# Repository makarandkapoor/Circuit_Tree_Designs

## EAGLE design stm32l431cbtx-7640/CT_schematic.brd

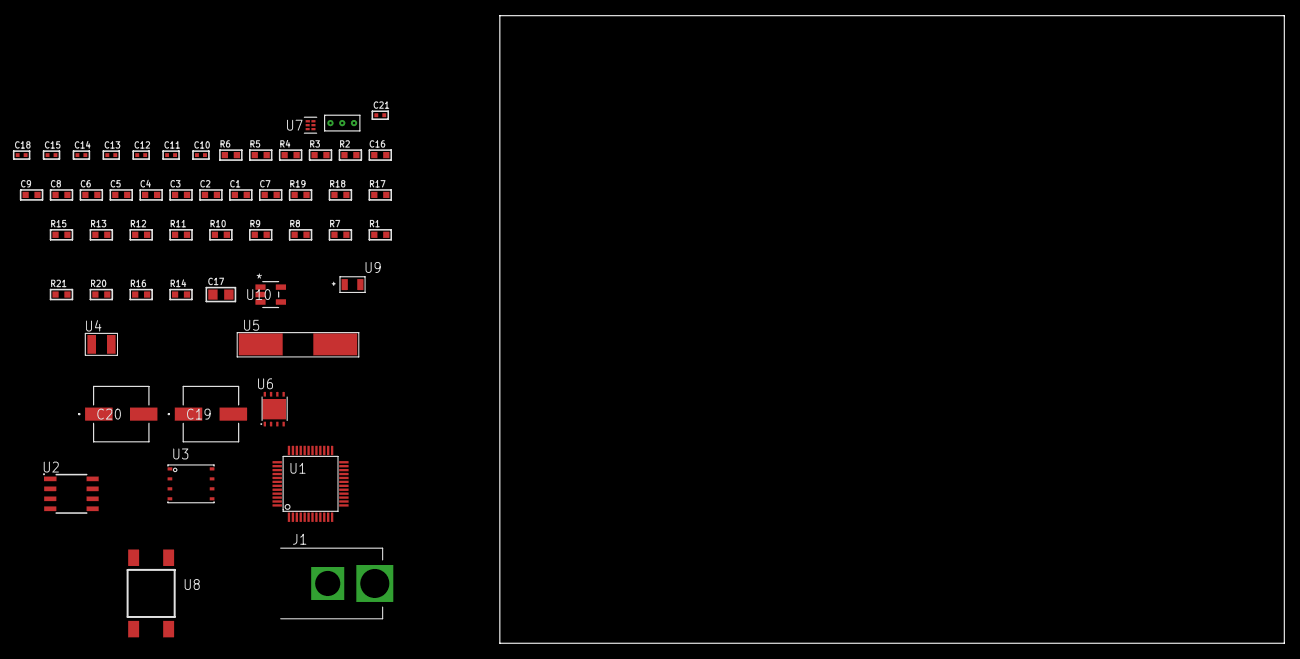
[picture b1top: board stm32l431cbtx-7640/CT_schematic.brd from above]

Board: 2 copper layers, 100.0 x 80.0 mm, 54 parts (0 on the bottom side), 30 nets, no tracks yet.

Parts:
C1, C9: 1e-06; C0603
C2, C3, C4, C5, C6: 1e-07; C0603
C7: 4.7e-06; C0603
C8: 1e-08; C0603
C10, C11, C12, C13: 1e-11; C0402
C14, C15, C21: 1e-08; C0402
C16: 8e-07; R0603
C17: 1e-05; C0805
C18: 1e-07; C0402
C19, C20: 0.0001; EXV-9H
J1: PJ-037B; PJ-037B_PACKAGE
R1, R7, R8, R9, R10, R11, R12, R13, R17, R18: 10000.0; R0603
R2: 1000.0; R0603
R3: 910.0; R0603
R4: 4700.0; R0603
R5, R6: 2200.0; R0603
R14, R16: 100000.0; R0603
R15: 36000.0; R0603
R19: 82000.0; R0603
R20: 300000.0; R0603
R21: 120000.0; R0603
U1: STM32L431CBT6; LQFP48
U2: AT25256B-SSHL-T; SOIC-8
U3: 24AA256-I/MF; DFN8-S
U4: ABS07-32.768KHZ-7-T
U5: ABLS-25.000MHZ-B2F-T
U6: LP2951ACSDX/NOPB; WSON-8
U7: TPS3895ADRYR; SON-6
U8: 4-1437565-2; SW_4-1437565-2
U9: Q65110A2395; LGM67K-G1J2-24-Z
U10: nc7sz125m5x; NC7SZ125M5X
U11: Dummy; DUMMY_PACKAGE_111

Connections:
CLK_CRYSTAL_U1_3: C10.1, U1.3, U4.1
CLK_CRYSTAL_U1_4: C11.1, U1.4, U4.2
CLK_CRYSTAL_U1_5: C12.1, U1.5, U5.1
CLK_CRYSTAL_U1_6: C13.1, U1.6, U5.2
GND: C1.2, C2.2, C3.2, C4.2, C5.2, C6.2, C7.2, C8.2, C9.2, C10.2, C11.2, C12.2, C13.2, C14.2, C15.2, C16.2, C17.2, C18.2, C19.2, C20.2, C21.2, J1.2, R2.2, R7.2, R11.2, R12.2, R16.2, R19.2, R21.2, U1.8, U1.23, U1.35, U1.47, U2.4, U3.4, U6.3, U6.4, U6.PAD, U7.2, U9.C, U10.1, U10.3, U11.1
NET_U1_7: R4.1, U1.7, U10.4
NET_U1_30: R5.1, U1.30, U3.6
NET_U1_31: R6.1, U1.31, U3.5
NET_U1_44: R7.1, U1.44
NET_U1_45: R3.1, U1.45, U9.A
NET_U1_46: R1.1, U1.46, U8.3, U8.4
NET_U2_3: R8.1, U2.3
NET_U2_7: R10.1, U2.7
NET_U3_1: R11.1, U3.1
NET_U3_2: R12.1, U3.2
NET_U3_3: R13.1, U3.3
NET_U6_5: R14.1, U6.5
NET_U6_7: R15.2, R16.1, U6.7
NET_U7_1: R18.1, R19.1, U7.1
NET_U7_3: R20.2, R21.1, U7.3
NET_U7_4: R17.1, U7.4, U10.2
NET_U8_1: R2.1, U8.1, U8.2
PROC_ADC1_IN10: U1.15, U11.2
PROC_ADC1_IN16: U1.19, U11.3
PROC_SPI1_MISO: U1.16, U2.2
PROC_SPI1_MOSI: U1.17, U2.5
PROC_SPI1_NSS: R9.1, U1.14, U2.1
PROC_SPI1_SCK: U1.11, U2.6
VCC_S1_12V7: C16.1, C19.1, C20.1, J1.1, U6.8
VCC_TIER1_1V8: C1.1, C2.1, C3.1, C4.1, C5.1, C6.1, C7.1, C8.1, C9.1, C14.1, C15.1, C17.1, C18.1, C21.1, R1.2, R3.2, R4.2, R5.2, R6.2, R8.2, R9.2, R10.2, R13.2, R14.2, R15.1, R17.2, R18.2, R20.1, U1.1, U1.9, U1.24, U1.36, U1.48, U2.8, U3.7, U3.8, U6.1, U7.6, U10.5

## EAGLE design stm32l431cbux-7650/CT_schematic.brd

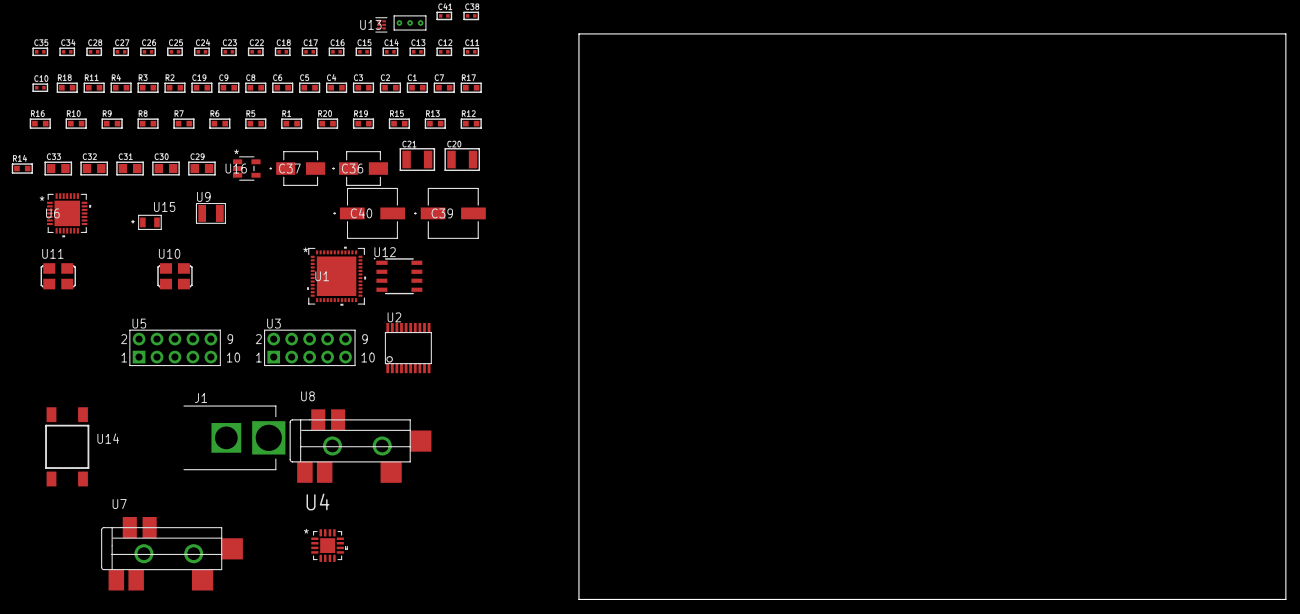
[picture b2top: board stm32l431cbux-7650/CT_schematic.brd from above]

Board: 2 copper layers, 100.0 x 80.0 mm, 79 parts (0 on the bottom side), 50 nets, no tracks yet.

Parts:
C1, C9, C19: 1e-06; C0603
C2, C3, C4, C5, C6: 1e-07; C0603
C7: 4.7e-06; C0603
C8: 1e-08; C0603
C10, C11: 1e-11; C0402
C12, C13, C14, C15, C16, C17, C18, C24, C25, C26, C27, C28, C38: 1e-07; C0402
C20, C21: 2.2e-05; C1210
C22, C23: 1e-09; C0402
C29, C30, C31, C32, C33: 1e-05; C0805
C34, C35, C41: 1e-08; C0402
C36: 1e-06; EXV-9B
C37: 2.2e-06; EXV-9B
C39, C40: 0.0001; EXV-9H
J1: PJ-037B; PJ-037B_PACKAGE
R1, R5, R6, R7, R16, R17: 10000.0; R0603
R2: 1000.0; R0603
R3: 1600.5; R0603
R4: 4700.0; R0603
R8, R9, R10: 47000.0; R0603
R11: 680.0; R0603
R12, R13, R15: 100000.0; R0603
R14: 164658.62; R0603
R18: 9100.0; R0603
R19: 680000.0; R0603
R20: 120000.0; R0603
U1: STM32L431CBU6; UFQFPN48
U2: SP3203ECY-L/TR; TSSOP20-I
U3, U5: HTSS-105-01-G-D
U4: TSC2008TRGVRQ1; QFN65P400X400X100-17N
U6: WM8731CLSEFL; QFN-28
U7, U8: SJ-43515TS-SMT-TR
U9: ABS07-32.768KHZ-7-T
U10: ASFL1-12.288MHZ-EC-T; ASFL1
U11: ASFL1-25MHZ-NCS; ASFL1
U12: LP2954AIMX/NOPB; LP2954
U13: TPS3895ADRYR; SON-6
U14: 4-1437565-2; SW_4-1437565-2
U15: Q65110A2395; LGM67K-G1J2-24-Z
U16: nc7sz125m5x; NC7SZ125M5X
U17: Dummy; DUMMY_PACKAGE_160

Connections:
CLK_CRYSTAL_U1_3: C10.1, U1.3, U9.1
CLK_CRYSTAL_U1_4: C11.1, U1.4, U9.2
CLK_U1_5: U1.5, U11.3
CLK_U6_1: U6.1, U10.3
GND: C1.2, C2.2, C3.2, C4.2, C5.2, C6.2, C7.2, C8.2, C9.2, C10.2, C11.2, C12.2, C13.2, C16.2, C17.2, C18.2, C19.2, C23.2, C24.2, C25.2, C26.2, C27.2, C28.2, C29.2, C30.2, C31.2, C32.2, C33.2, C34.2, C35.2, C36.2, C37.2, C38.2, C39.2, C40.2, C41.2, J1.2, R2.2, R5.2, R8.2, R9.2, R10.2, R15.2, R18.2, R20.2, U1.8, U1.23, U1.35, U1.47, U1.49, U2.18, U3.9, U4.10, U4.12, U4.17, U5.9, U6.4, U6.15, U6.19, U6.25, U6.26, U6.29, U7.1, U8.1, U10.2, U11.2, U12.4, U13.2, U15.C, U16.1, U16.3, U17.1
NET_U1_7: R4.1, U1.7, U16.4
NET_U1_44: R5.1, U1.44
NET_U1_45: R3.1, U1.45, U15.A
NET_U1_46: R1.1, U1.46, U14.3, U14.4
NET_U2_1: C14.1, U2.1
NET_U2_2: C16.1, U2.2
NET_U2_3: C14.2, U2.3
NET_U2_4: C15.1, U2.4
NET_U2_5: C15.2, U2.5
NET_U2_6: C17.1, U2.6
NET_U3_3: U2.14, U3.3
NET_U3_4: U2.13, U3.4
NET_U3_5: U2.17, U3.5
NET_U3_6: U2.16, U3.6
NET_U4_15: R7.1, U4.15
NET_U5_3: U4.7, U5.3
NET_U5_4: U4.9, U5.4
NET_U5_5: U4.6, U5.5
NET_U5_6: U4.8, U5.6
NET_U6_20: C28.1, C33.1, U6.20
NET_U7_2: C21.1, R9.1, U7.2
NET_U7_5: C20.1, R8.1, U7.5
NET_U8_5: C22.1, C23.1, R10.1, R11.1, U8.5
NET_U12_3: R13.1, U12.3
NET_U12_5: R12.1, U12.5
NET_U12_7: R14.2, R15.1, U12.7
NET_U13_1: R17.1, R18.1, U13.1
NET_U13_3: R19.2, R20.1, U13.3
NET_U13_4: R16.1, U13.4, U16.2
NET_U14_1: R2.1, U14.1, U14.2
PROC_LPUART1_CTS: U1.16, U2.8
PROC_LPUART1_RTS: U1.19, U2.10
PROC_LPUART1_RX: U1.13, U2.11
PROC_LPUART1_TX: U1.12, U2.7
PROC_SAI1_FS_A: U1.25, U6.9, U6.11
PROC_SAI1_SCK_A: U1.21, U6.7
PROC_SAI1_SD_A: U1.28, U6.8
PROC_SPI1_MISO: U1.32, U4.16
PROC_SPI1_MOSI: U1.17, U4.2
PROC_SPI1_NSS: R6.1, U1.14, U4.3
PROC_SPI1_SCK: U1.11, U4.4
PROC_TIM1_CH2: U1.30, U17.2
PROC_TIM1_CH2N: U1.18, U17.3
VCC_S1_6V3: C36.1, C39.1, C40.1, J1.1, R13.2, U12.8
VCC_TIER1_3V3: C1.1, C2.1, C3.1, C4.1, C5.1, C6.1, C7.1, C8.1, C9.1, C12.1, C13.1, C18.1, C19.1, C24.1, C25.1, C26.1, C27.1, C29.1, C30.1, C31.1, C32.1, C34.1, C35.1, C37.1, C38.1, C41.1, R1.2, R3.2, R4.2, R6.2, R7.2, R12.2, R14.1, R16.2, R17.2, R19.1, U1.1, U1.9, U1.24, U1.36, U1.48, U2.12, U2.19, U4.5, U6.3, U6.5, U6.12, U6.18, U10.4, U11.4, U12.1, U13.6, U16.5

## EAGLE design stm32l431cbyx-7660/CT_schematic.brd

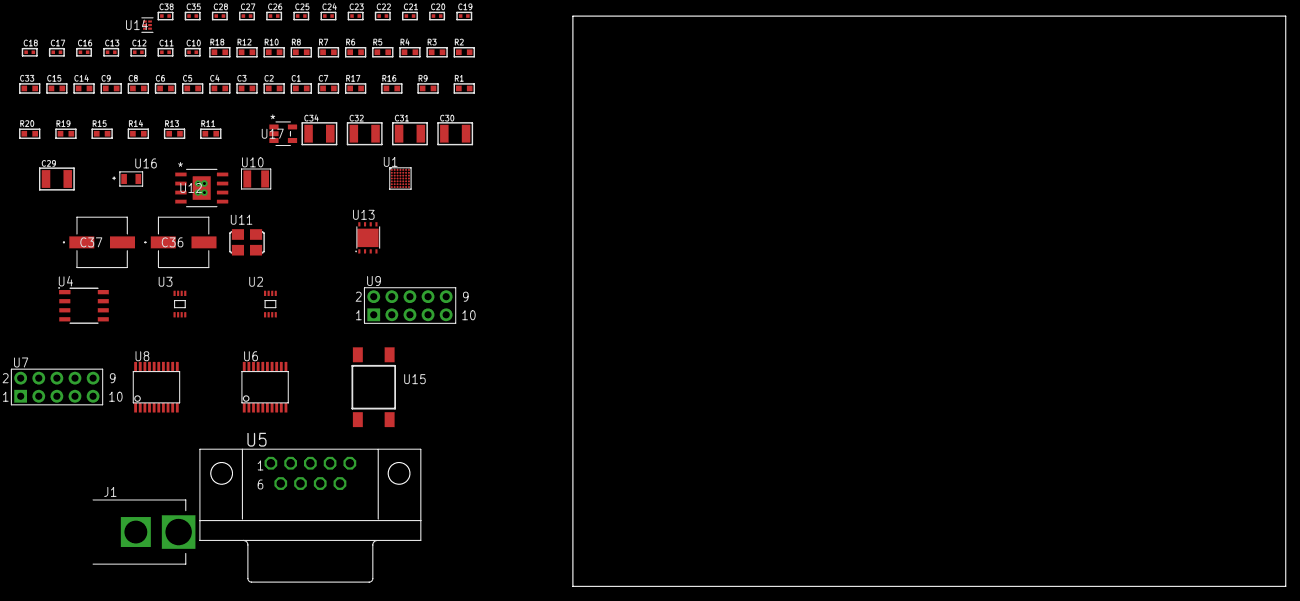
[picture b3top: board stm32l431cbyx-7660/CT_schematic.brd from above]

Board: 2 copper layers, 100.0 x 80.0 mm, 76 parts (0 on the bottom side), 55 nets, no tracks yet.

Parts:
C1, C9, C14, C15, C33: 1e-06; C0603
C2, C3, C4, C5, C6: 1e-07; C0603
C7: 4.7e-06; C0603
C8: 1e-08; C0603
C10, C11: 1e-11; C0402
C12, C13, C28, C38: 1e-08; C0402
C16, C17, C18, C19, C20, C21, C22, C23, C24, C25, C26, C27, C35: 1e-07; C0402
C29, C30, C31, C32, C34: 1e-05; C1210
C36, C37: 0.0001; EXV-9H
J1: PJ-037B; PJ-037B_PACKAGE
R1, R9, R16, R17: 10000.0; R0603
R2: 1000.0; R0603
R3: 1600.5; R0603
R4: 4700.0; R0603
R5, R6, R7, R8, R12: 2200.0; R0603
R10: 120.0; R0603
R11: 4031.5447154472; R0603
R13, R15: 100000.0; R0603
R14: 300000.0; R0603
R18: 9100.0; R0603
R19: 680000.0; R0603
R20: 120000.0; R0603
U1: STM32L431CBYx; WLCSP48
U2: 24AA01T-I/MNY; TDFN-8/6MM
U3: 24AA04-I/MC; TDFN-8/6MM
U4: MCP2562-E/SN; SOIC-8
U5: 182-009-113R531; 182-009-MALE
U6, U8: SP3203ECY-L/TR; TSSOP20-I
U7, U9: HTSS-105-01-G-D
U10: ABS07-32.768KHZ-7-T
U11: ASFL1-25MHZ-NCS; ASFL1
U12: MIC5234YME; SOIC-8_EP
U13: LP2951ACSDX/NOPB; WSON-8
U14: TPS3895ADRYR; SON-6
U15: 4-1437565-2; SW_4-1437565-2
U16: Q65110A2395; LGM67K-G1J2-24-Z
U17: nc7sz125m5x; NC7SZ125M5X

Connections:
CLK_CRYSTAL_U1_C6: C10.1, U1.C6, U10.1
CLK_CRYSTAL_U1_C7: C11.1, U1.C7, U10.2
CLK_U1_D7: U1.D7, U11.3
GND: C1.2, C2.2, C3.2, C4.2, C5.2, C6.2, C7.2, C8.2, C9.2, C10.2, C11.2, C12.2, C13.2, C14.2, C15.2, C16.2, C17.2, C20.2, C21.2, C22.2, C23.2, C26.2, C27.2, C28.2, C29.2, C30.2, C31.2, C32.2, C33.2, C34.2, C35.2, C36.2, C37.2, C38.2, J1.2, R2.2, R9.2, R12.2, R15.2, R18.2, R20.2, U1.A6, U1.B1, U1.E7, U1.G2, U2.4, U3.4, U4.2, U4.8, U5.5, U6.18, U7.9, U8.18, U9.9, U11.2, U12.7, U12.EPAD, U13.3, U13.4, U13.PAD, U14.2, U16.C, U17.1, U17.3
NET_U1_A5: R9.1, U1.A5
NET_U1_C2: R6.1, U1.C2, U3.5
NET_U1_D2: R5.1, U1.D2, U3.6
NET_U1_D5: R4.1, U1.D5, U17.4
NET_U1_E1: R8.1, U1.E1, U2.5
NET_U1_E3: R7.1, U1.E3, U2.6
NET_U1_G6: R3.1, U1.G6, U16.A
NET_U1_G7: R1.1, U1.G7, U15.3, U15.4
NET_U4_6: R10.2, U4.6
NET_U5_2: R10.2, U4.6, U5.2
NET_U5_3: R10.1, U4.7, U5.3
NET_U6_1: C18.1, U6.1
NET_U6_2: C20.1, U6.2
NET_U6_3: C18.2, U6.3
NET_U6_4: C19.1, U6.4
NET_U6_5: C19.2, U6.5
NET_U6_6: C21.1, U6.6
NET_U7_3: U6.14, U7.3
NET_U7_4: U6.13, U7.4
NET_U7_5: U6.17, U7.5
NET_U7_6: U6.16, U7.6
NET_U8_1: C24.1, U8.1
NET_U8_2: C26.1, U8.2
NET_U8_3: C24.2, U8.3
NET_U8_4: C25.1, U8.4
NET_U8_5: C25.2, U8.5
NET_U8_6: C27.1, U8.6
NET_U9_3: U8.14, U9.3
NET_U9_4: U8.13, U9.4
NET_U9_5: U8.17, U9.5
NET_U9_6: U8.16, U9.6
NET_U12_4: R11.2, R12.1, U12.4
NET_U13_5: R13.1, U13.5
NET_U13_7: R14.2, R15.1, U13.7
NET_U14_1: R17.1, R18.1, U14.1
NET_U14_3: R19.2, R20.1, U14.3
NET_U14_4: R16.1, U14.4, U17.2
NET_U15_1: R2.1, U15.1, U15.2
PROC_CAN1_RX: U1.B5, U4.4
PROC_CAN1_TX: U1.C3, U4.1
PROC_LPUART1_CTS: U1.E2, U6.8
PROC_LPUART1_RTS: U1.F1, U6.10
PROC_LPUART1_RX: U1.E4, U6.11
PROC_LPUART1_TX: U1.E5, U6.7
PROC_USART1_CTS: U1.A4, U8.8
PROC_USART1_RTS: U1.A3, U8.10
PROC_USART1_RX: U1.D4, U8.11
PROC_USART1_TX: U1.C4, U8.7
VCC_S1_6V1: C29.1, C30.1, C33.1, C36.1, C37.1, J1.1, U12.5, U12.8, U13.8
VCC_TIER1_3V3: C1.1, C2.1, C3.1, C4.1, C5.1, C6.1, C7.1, C8.1, C9.1, C12.1, C13.1, C15.1, C16.1, C17.1, C22.1, C23.1, C28.1, C31.1, C32.1, C35.1, C38.1, R1.2, R3.2, R4.2, R5.2, R6.2, R7.2, R8.2, R11.1, R16.2, R17.2, R19.1, U1.A1, U1.A7, U1.B6, U1.F7, U1.G1, U2.7, U2.8, U3.7, U3.8, U4.5, U6.12, U6.19, U8.12, U8.19, U11.4, U12.1, U14.6, U17.5
VCC_TIER1_5V0: C14.1, C34.1, R13.2, R14.1, U4.3, U13.1

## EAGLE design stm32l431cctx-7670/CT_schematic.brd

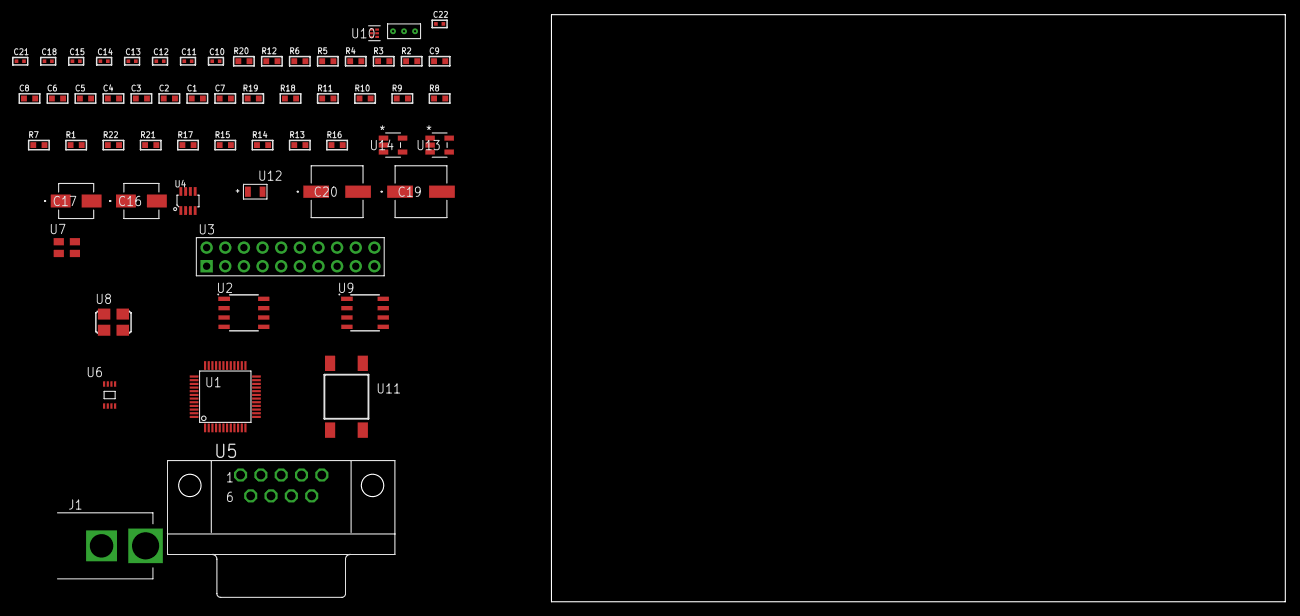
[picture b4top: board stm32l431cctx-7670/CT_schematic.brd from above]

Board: 2 copper layers, 100.0 x 80.0 mm, 60 parts (0 on the bottom side), 36 nets, no tracks yet.

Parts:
C1, C9: 1e-06; C0603
C2, C3, C4, C5, C6: 1e-07; C0603
C7: 4.7e-06; C0603
C8: 1e-08; C0603
C10, C13, C14, C15, C21, C22: 1e-08; C0402
C11, C12, C18: 1e-07; C0402
C16: 1e-06; EXV-9B
C17: 2.2e-06; EXV-9B
C19, C20: 0.0001; EXV-9H
J1: PJ-037B; PJ-037B_PACKAGE
R1, R7, R8, R9, R10, R11, R18, R19: 10000.0; R0603
R2: 1000.0; R0603
R3: 1600.5; R0603
R4: 4700.0; R0603
R5, R6: 2200.0; R0603
R12: 120.0; R0603
R13, R14, R15, R17: 100000.0; R0603
R16: 164658.62; R0603
R20: 9100.0; R0603
R21: 680000.0; R0603
R22: 120000.0; R0603
U1: STM32L431CCT6; LQFP48
U2: AT25080B-SSHL-T; SOIC-8
U3: TST-110-05-T-D-RA
U4: MAX3051EKA+T; SOT-23-8
U5: 182-009-113R531; 182-009-MALE
U6: 24AA02T-I/MNY; TDFN-8/6MM
U7: ASEK-32.768KHz-ECST; ASEK
U8: ASFL1-25MHZ-NCS; ASFL1
U9: LP2954AIMX/NOPB; LP2954
U10: TPS3895ADRYR; SON-6
U11: 4-1437565-2; SW_4-1437565-2
U12: Q65110A2395; LGM67K-G1J2-24-Z
U13, U14: nc7sz125m5x; NC7SZ125M5X
U15: Dummy; DUMMY_PACKAGE_129

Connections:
CLK_U1_3: U1.3, U7.3
CLK_U1_5: U1.5, U8.3
GND: C1.2, C2.2, C3.2, C4.2, C5.2, C6.2, C7.2, C8.2, C9.2, C10.2, C11.2, C12.2, C13.2, C14.2, C15.2, C16.2, C17.2, C18.2, C19.2, C20.2, C21.2, C22.2, J1.2, R2.2, R7.2, R13.2, R17.2, R20.2, R22.2, U1.8, U1.23, U1.35, U1.47, U2.4, U3.4, U3.6, U3.8, U3.10, U3.12, U3.14, U3.16, U3.18, U3.20, U4.2, U5.5, U6.4, U6.7, U7.2, U8.2, U9.4, U10.2, U12.C, U13.2, U13.3, U14.1, U14.3, U15.1
NET_U1_7: R4.1, U1.7, U14.4
NET_U1_30: R5.1, U1.30, U6.6
NET_U1_31: R6.1, U1.31, U6.5
NET_U1_44: R7.1, U1.44
NET_U1_45: R3.1, U1.45, U12.A
NET_U1_46: R1.1, U1.46, U11.3, U11.4
NET_U2_3: R8.1, U2.3
NET_U2_7: R10.1, U2.7
NET_U4_6: R12.2, U4.6
NET_U4_8: R13.1, U4.8
NET_U5_2: R12.2, U4.6, U5.2
NET_U5_3: R12.1, U4.7, U5.3
NET_U9_3: R15.1, U9.3
NET_U9_5: R14.1, U9.5
NET_U9_7: R16.2, R17.1, U9.7
NET_U10_1: R19.1, R20.1, U10.1
NET_U10_3: R21.2, R22.1, U10.3
NET_U10_4: R18.1, U10.4, U13.4, U14.2
NET_U11_1: R2.1, U11.1, U11.2
PROC_ADC1_IN10: U1.15, U15.2
PROC_ADC1_IN16: U1.19, U15.3
PROC_CAN1_RX: U1.32, U4.4
PROC_CAN1_TX: U1.33, U4.1
PROC_SPI1_MISO: U1.16, U2.2
PROC_SPI1_MOSI: U1.17, U2.5
PROC_SPI1_NSS: R9.1, U1.14, U2.1
PROC_SPI1_SCK: U1.11, U2.6
PROC_SYS_JTCK_SWCLK: U1.37, U3.9
PROC_SYS_JTDO_SWO: U1.39, U3.13
PROC_SYS_JTMS_SWDIO: U1.34, U3.7
RST_OUT_U3_SRESET_B: R11.1, U3.15, U13.1
VCC_S1_14V8: C16.1, C19.1, C20.1, J1.1, R15.2, U9.8
VCC_TIER1_3V3: C1.1, C2.1, C3.1, C4.1, C5.1, C6.1, C7.1, C8.1, C9.1, C10.1, C11.1, C12.1, C13.1, C14.1, C15.1, C17.1, C18.1, C21.1, C22.1, R1.2, R3.2, R4.2, R5.2, R6.2, R8.2, R9.2, R10.2, R11.2, R14.2, R16.1, R18.2, R19.2, R21.1, U1.1, U1.9, U1.24, U1.36, U1.48, U2.8, U3.1, U4.3, U6.8, U7.4, U8.4, U9.1, U10.6, U13.5, U14.5

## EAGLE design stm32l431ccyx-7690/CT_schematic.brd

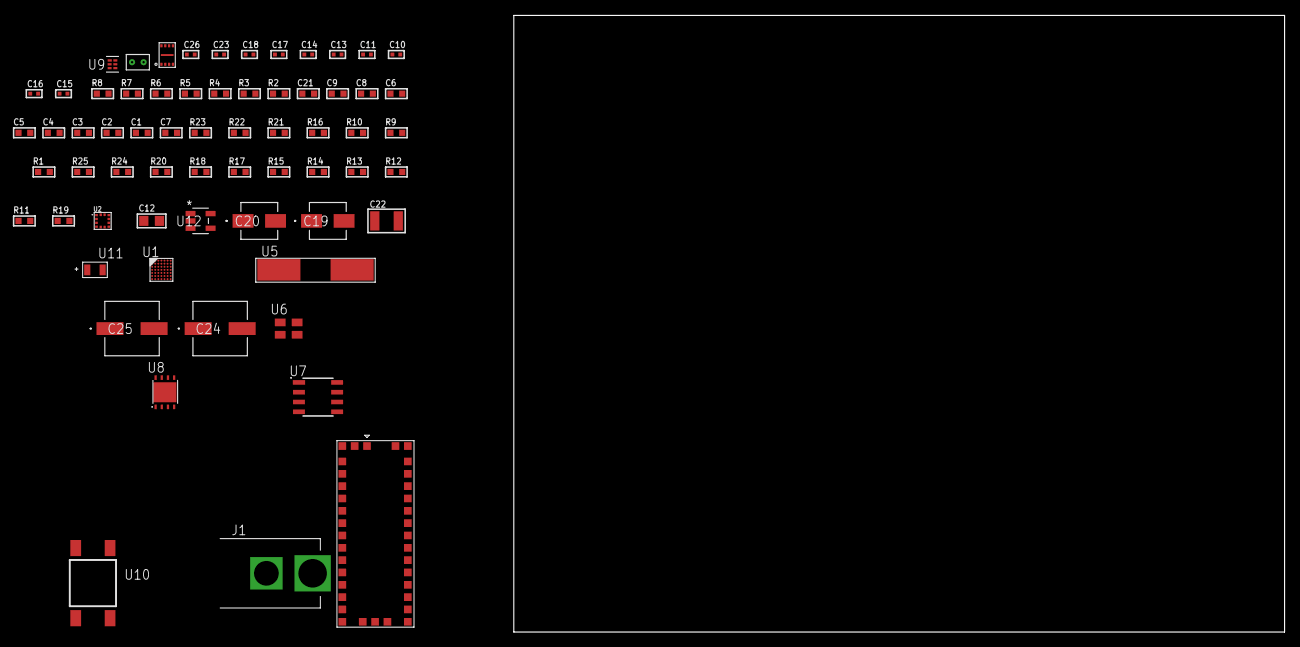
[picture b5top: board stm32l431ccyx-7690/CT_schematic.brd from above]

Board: 2 copper layers, 100.0 x 80.0 mm, 65 parts (0 on the bottom side), 32 nets, no tracks yet.

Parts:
C1, C9, C21: 1e-06; C0603
C2, C3, C4, C5, C6: 1e-07; C0603
C7: 4.7e-06; C0603
C8: 1e-08; C0603
C10, C11: 1e-11; C0402
C12: 1e-05; C0805
C13, C14, C17, C23: 1e-07; C0402
C15, C16: 2.2e-11; C0402
C18, C26: 1e-08; C0402
C19: 1e-06; EXV-9B
C20: 2.2e-06; EXV-9B
C22: 1e-05; C1210
C24, C25: 0.0001; EXV-9H
J1: PJ-037B; PJ-037B_PACKAGE
R1, R9, R10, R21, R22: 10000.0; R0603
R2: 1000.0; R0603
R3: 910.0; R0603
R4: 4700.0; R0603
R5, R6, R7, R8: 2200.0; R0603
R11, R12, R13, R14, R15, R17, R18, R20: 100000.0; R0603
R16: 47000.0; R0603
R19: 153694.38; R0603
R23: 82000.0; R0603
R24: 300000.0; R0603
R25: 120000.0; R0603
U1: STM32L431CCY6; WLCSP49
U2: LIS2HH12TR; LGA-12
U3: M10382
U4: SST26WF040BT-104I/NP; USON-8
U5: ABLS-25.000MHZ-B2F-T
U6: ASEK-32.768KHz-ECST; ASEK
U7: LP2954AIMX/NOPB; LP2954
U8: LP2951ACSDX/NOPB; WSON-8
U9: TPS3895ADRYR; SON-6
U10: 4-1437565-2; SW_4-1437565-2
U11: Q65110A2395; LGM67K-G1J2-24-Z
U12: nc7sz125m5x; NC7SZ125M5X
U13: Dummy; DUMMY_PACKAGE_140

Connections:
CLK_CRYSTAL_U1_D6: C10.1, U1.D6, U5.1
CLK_CRYSTAL_U1_D7: C11.1, U1.D7, U5.2
CLK_U1_C7: U1.C7, U6.3
GND: C1.2, C2.2, C3.2, C4.2, C5.2, C6.2, C7.2, C8.2, C9.2, C10.2, C11.2, C12.2, C13.2, C14.2, C15.2, C16.2, C17.2, C18.2, C19.2, C20.2, C21.2, C22.2, C23.2, C24.2, C25.2, C26.2, J1.2, R2.2, R9.2, R17.2, R20.2, R23.2, R25.2, U1.A6, U1.B1, U1.E7, U1.G2, U2.5, U2.6, U2.7, U2.8, U3.2, U3.4, U3.14, U3.17, U3.21, U3.24, U3.26, U3.28, U3.33, U3.34, U3.35, U3.36, U4.4, U4.9, U6.2, U7.4, U8.3, U8.4, U8.PAD, U9.2, U11.C, U12.1, U12.3, U13.1
NET_U1_A5: R9.1, U1.A5
NET_U1_B5: R5.1, U1.B5, U3.19
NET_U1_C2: R6.1, U1.C2, U3.18
NET_U1_D5: R4.1, U1.D5, U12.4
NET_U1_E1: R8.1, U1.E1, U2.4
NET_U1_E2: R7.1, U1.E2, U2.1
NET_U1_G6: R3.1, U1.G6, U11.A
NET_U1_G7: R1.1, U1.G7, U10.3, U10.4
NET_U2_2: R10.1, U2.2
NET_U7_3: R15.1, U7.3
NET_U7_5: R14.1, U7.5
NET_U7_7: R16.2, R17.1, U7.7
NET_U8_5: R18.1, U8.5
NET_U8_7: R19.2, R20.1, U8.7
NET_U9_1: R22.1, R23.1, U9.1
NET_U9_3: R24.2, R25.1, U9.3
NET_U9_4: R21.1, U9.4, U12.2
NET_U10_1: R2.1, U10.1, U10.2
PROC_DAC1_OUT2: U1.F5, U13.2
PROC_QUADSPI_BK1_IO0: U1.G4, U4.5
PROC_QUADSPI_BK1_IO1: U1.G5, U4.2
PROC_QUADSPI_BK1_IO2: R12.1, U1.F3, U4.3
PROC_QUADSPI_BK1_IO3: R13.1, U1.F4, U4.7
PROC_QUADSPI_BK1_NCS: R11.1, U1.E5, U4.1
PROC_QUADSPI_CLK: U1.E3, U4.6
VCC_S1_8V4: C19.1, C21.1, C24.1, C25.1, J1.1, R15.2, U7.8, U8.8
VCC_TIER1_1V8: C1.1, C2.1, C3.1, C4.1, C5.1, C6.1, C7.1, C8.1, C9.1, C12.1, C13.1, C14.1, C15.1, C16.1, C17.1, C20.1, C23.1, C26.1, R1.2, R3.2, R4.2, R5.2, R6.2, R7.2, R8.2, R10.2, R11.2, R12.2, R13.2, R14.2, R16.1, R21.2, R22.2, R24.1, U1.A1, U1.A7, U1.B6, U1.F7, U1.G1, U2.9, U2.10, U3.5, U3.25, U3.27, U4.8, U7.1, U9.6, U12.5
VCC_TIER1_3V3: C18.1, C22.1, R18.2, R19.1, U6.4, U8.1

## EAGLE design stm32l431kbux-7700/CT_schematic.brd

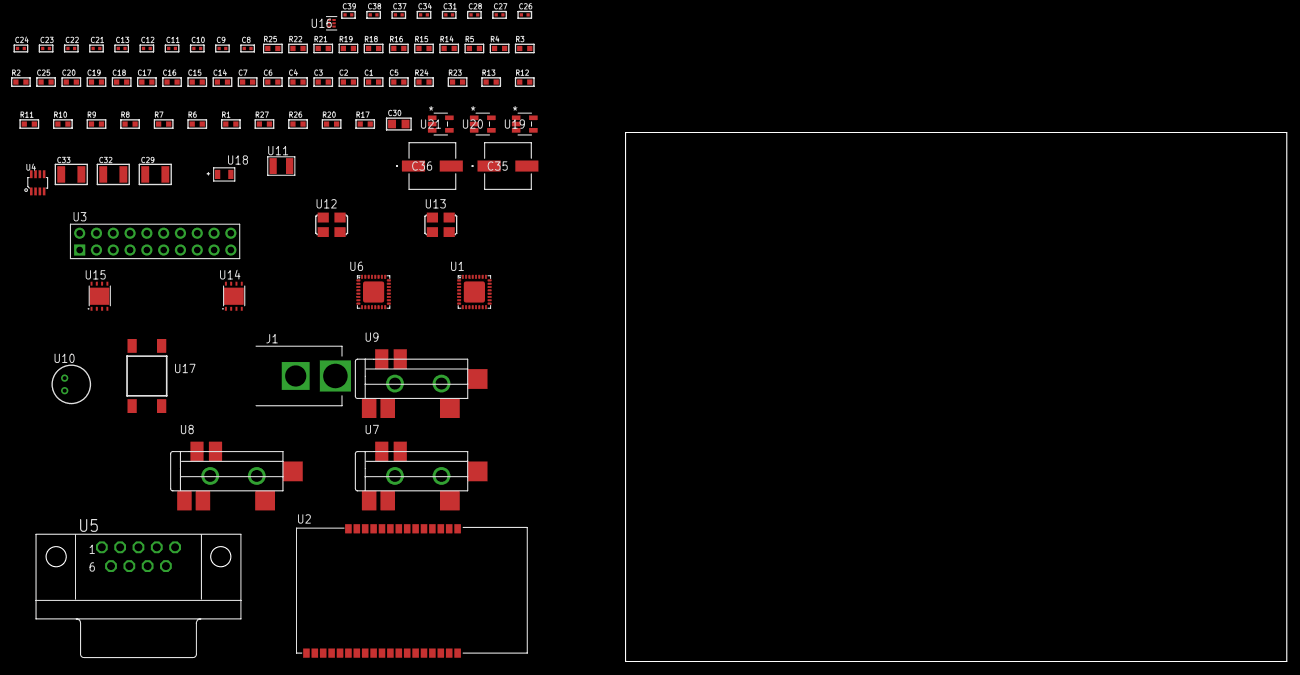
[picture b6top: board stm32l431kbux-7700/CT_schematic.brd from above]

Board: 2 copper layers, 100.0 x 80.0 mm, 88 parts (0 on the bottom side), 55 nets, no tracks yet.

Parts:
C1, C2, C3, C4: 1e-07; C0603
C5: 4.7e-06; C0603
C6: 1e-08; C0603
C7, C14, C15, C16, C17, C18, C19, C20, C25: 1e-06; C0603
C8, C9: 1e-11; C0402
C10, C11, C12, C13, C21, C22, C23, C24, C34: 1e-07; C0402
C26, C27, C28, C31, C37, C38, C39: 1e-08; C0402
C29, C32, C33: 1e-05; C1210
C30: 1e-05; C0805
C35, C36: 0.0001; EXV-9H
J1: PJ-037B; PJ-037B_PACKAGE
R1, R6, R7, R8, R9, R10, R11, R12, R13, R23, R24: 10000.0; R0603
R2, R19, R22: 1000.0; R0603
R3: 1600.5; R0603
R4, R5: 4700.0; R0603
R14: 120.0; R0603
R15, R16: 1270.0; R0603
R17, R20: 100000.0; R0603
R18: 200.0; R0603
R21: 2231.0; R0603
R25: 9100.0; R0603
R26: 680000.0; R0603
R27: 120000.0; R0603
U1: STM32L431KBU6; QFN-32
U2: ETRX3587
U3: TST-110-05-T-D-RA
U4: MAX3051EKA+T; SOT-23-8
U5: 182-009-113R531; 182-009-MALE
U6: SGTL5000XNAA3; QFN-32
U7, U8, U9: SJ-43515TS-SMT-TR
U10: WM-64PCT; WM-64PC
U11: ABS07-32.768KHZ-7-T
U12: ASFL1-12MHZ-NCS; ASFL1
U13: ASFL-24.57MHZ-NCS; ASFL1
U14, U15: LP3878SDX-ADJ/NOPB; WSON-8
U16: TPS3895ADRYR; SON-6
U17: 4-1437565-2; SW_4-1437565-2
U18: Q65110A2395; LGM67K-G1J2-24-Z
U19, U20, U21: nc7sz125m5x; NC7SZ125M5X

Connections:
CLK_CRYSTAL_U1_2: C8.1, U1.2, U11.1
CLK_CRYSTAL_U1_3: C9.1, U1.3, U11.2
CLK_U1_6: U1.6, U12.3
CLK_U6_21: U6.21, U13.3
GND: C1.2, C2.2, C3.2, C4.2, C5.2, C6.2, C7.2, C8.2, C9.2, C10.2, C11.2, C12.2, C13.2, C21.2, C22.2, C23.2, C24.2, C25.2, C26.2, C27.2, C28.2, C29.2, C30.2, C31.2, C32.2, C33.2, C34.2, C35.2, C36.2, C37.2, C38.2, C39.2, J1.2, R2.2, R6.2, R7.2, R13.2, R16.2, R19.2, R22.2, R25.2, R27.2, U1.16, U1.32, U1.EXP, U2.1, U2.13, U2.19, U2.20, U2.31, U2.33, U3.4, U3.6, U3.8, U3.10, U3.12, U3.14, U3.16, U3.18, U3.20, U4.2, U4.8, U5.5, U6.1, U6.3, U6.7, U6.EXP, U8.1, U9.1, U10.2, U12.2, U13.2, U14.3, U14.PAD, U15.3, U15.PAD, U16.2, U18.C, U19.2, U19.3, U20.1, U20.3, U21.1, U21.3
NET_U1_4: R5.1, U1.4, U21.4
NET_U1_30: R3.1, U1.30, U18.A
NET_U1_31: R1.1, R6.1, U1.31, U17.3, U17.4
NET_U2_7: R4.1, U2.7, U20.4
NET_U2_21: R7.1, U2.21
NET_U3_19: R13.1, U3.19
NET_U4_6: R14.2, U4.6
NET_U5_2: R14.2, U4.6, U5.2
NET_U5_3: R14.1, U4.7, U5.3
NET_U6_10: C24.1, U6.10
NET_U6_29: R15.1, U6.29
NET_U6_31: R16.1, U6.31
NET_U7_1: U6.4, U7.1
NET_U7_2: U6.2, U7.2
NET_U7_5: U6.6, U7.5
NET_U8_2: C15.1, U8.2
NET_U8_5: C14.1, U8.5
NET_U9_2: C17.1, C18.1, U9.2
NET_U9_5: C16.1, U9.5
NET_U9_13: C17.2, C18.2
NET_U10_1: C19.1, C20.1, C25.1, U6.16, U10.1
NET_U10_15: C19.2, C20.2
NET_U14_1: C28.1, U14.1
NET_U14_6: R18.2, R19.1, U14.6
NET_U14_8: R17.1, U14.8
NET_U15_1: C31.1, U15.1
NET_U15_6: R21.2, R22.1, U15.6
NET_U15_8: R20.1, U15.8
NET_U16_1: R24.1, R25.1, U16.1
NET_U16_3: R26.2, R27.1, U16.3
NET_U16_4: R23.1, U16.4, U19.4, U20.2, U21.2
NET_U17_1: R2.1, U17.1, U17.2
PROC_CAN1_RX: U1.21, U4.4
PROC_CAN1_TX: U1.22, U4.1
PROC_LPUART1_CTS: U1.12, U2.8
PROC_LPUART1_RTS: U1.15, U2.6
PROC_LPUART1_RX: U1.9, U2.17
PROC_LPUART1_TX: U1.8, U2.18
PROC_SAI1_FS_A: U1.19, U6.23
PROC_SAI1_SCK_A: U1.18, U6.24
PROC_SAI1_SD_A: U1.20, U6.26
PROC_SYS_JTCK_SWCLK: R11.1, U1.24, U3.9
PROC_SYS_JTDI: R9.1, U1.25, U3.5
PROC_SYS_JTDO_SWO: U1.26, U3.13
PROC_SYS_JTMS_SWDIO: R10.1, U1.23, U3.7
PROC_SYS_JTRST: R8.1, U1.27, U3.3
RST_OUT_U3_SRESET_B: R12.1, U3.15, U19.1
VCC_S1_15V4: C29.1, C32.1, C35.1, C36.1, J1.1, R17.2, R20.2, U14.4, U15.4
VCC_TIER1_1V2: C21.1, C30.1, R18.1, U6.30, U14.5
VCC_TIER1_3V3: C1.1, C2.1, C3.1, C4.1, C5.1, C6.1, C7.1, C10.1, C11.1, C12.1, C13.1, C22.1, C23.1, C26.1, C27.1, C33.1, C34.1, C37.1, C38.1, C39.1, R1.2, R3.2, R4.2, R5.2, R8.2, R9.2, R10.2, R11.2, R12.2, R15.2, R21.1, R23.2, R24.2, R26.1, U1.1, U1.5, U1.17, U2.32, U3.1, U3.2, U4.3, U6.5, U6.20, U12.4, U13.4, U15.5, U16.6, U19.5, U20.5, U21.5

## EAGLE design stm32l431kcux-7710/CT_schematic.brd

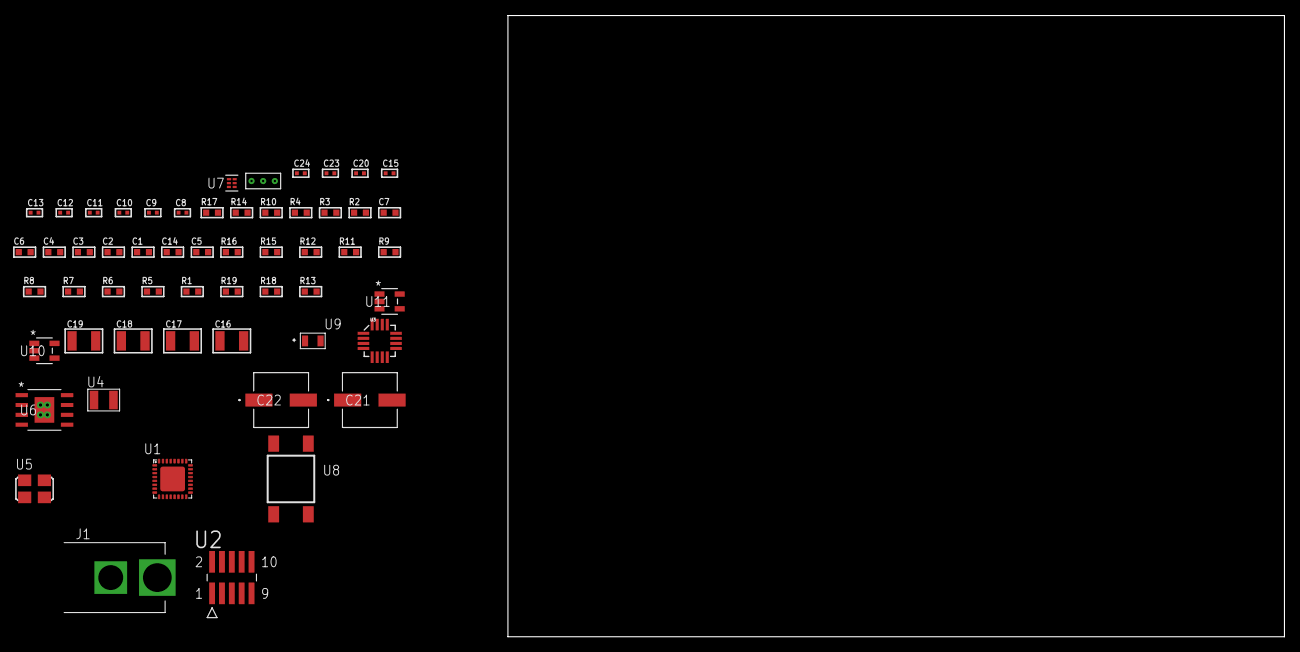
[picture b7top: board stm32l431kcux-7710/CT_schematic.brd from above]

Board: 2 copper layers, 100.0 x 80.0 mm, 56 parts (0 on the bottom side), 27 nets, no tracks yet.

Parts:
C1, C2, C3, C4: 1e-07; C0603
C5: 4.7e-06; C0603
C6: 1e-08; C0603
C7: 1e-06; C0603
C8, C9: 1e-11; C0402
C10, C20: 1e-07; C0402
C11, C12, C13, C15, C23, C24: 1e-08; C0402
C14: 4.7e-07; C0603
C16, C17, C18, C19: 1e-05; C1210
C21, C22: 0.0001; EXV-9H
J1: PJ-037B; PJ-037B_PACKAGE
R1, R5, R6, R7, R8, R9, R11, R12, R15, R16: 10000.0; R0603
R2: 1000.0; R0603
R3: 1600.5; R0603
R4: 4700.0; R0603
R10: 5.0; R0603
R13: 4031.5447154472; R0603
R14: 2200.0; R0603
R17: 9100.0; R0603
R18: 680000.0; R0603
R19: 120000.0; R0603
U1: STM32L431KCU6; QFN-32
U2: FTSH-105-01-L-DV-K; SAMTEC_FTSH-105-01-L-DV-K
U3: l3g4200d; LGA-16
U4: ABS07-32.768KHZ-7-T
U5: ASFL1-12MHZ-NCS; ASFL1
U6: MIC5234YME; SOIC-8_EP
U7: TPS3895ADRYR; SON-6
U8: 4-1437565-2; SW_4-1437565-2
U9: Q65110A2395; LGM67K-G1J2-24-Z
U10, U11: nc7sz125m5x; NC7SZ125M5X
U12: Dummy; DUMMY_PACKAGE_118

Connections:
CLK_CRYSTAL_U1_2: C8.1, U1.2, U4.1
CLK_CRYSTAL_U1_3: C9.1, U1.3, U4.2
CLK_U1_6: U1.6, U5.3
GND: C1.2, C2.2, C3.2, C4.2, C5.2, C6.2, C7.2, C8.2, C9.2, C10.2, C11.2, C12.2, C13.2, C15.2, C16.2, C17.2, C18.2, C19.2, C20.2, C21.2, C22.2, C23.2, C24.2, J1.2, R2.2, R5.2, R9.2, R10.2, R11.1, R11.2, R14.2, R17.2, R19.2, U1.16, U1.32, U1.EXP, U2.3, U2.5, U3.8, U3.9, U3.10, U3.11, U3.12, U3.13, U5.2, U6.7, U6.EPAD, U7.2, U9.C, U10.2, U10.3, U11.1, U11.3, U12.1
NET_U1_4: R4.1, U1.4, U11.4
NET_U1_30: R3.1, U1.30, U9.A
NET_U1_31: R1.1, R5.1, U1.31, U8.3, U8.4
NET_U2_9: R10.1, U2.9
NET_U3_14: C13.1, C14.1, U3.14
NET_U6_4: R13.2, R14.1, U6.4
NET_U7_1: R16.1, R17.1, U7.1
NET_U7_3: R18.2, R19.1, U7.3
NET_U7_4: R15.1, U7.4, U10.4, U11.2
NET_U8_1: R2.1, U8.1, U8.2
PROC_SPI1_MISO: U1.12, U3.4
PROC_SPI1_MOSI: U1.13, U3.3
PROC_SPI1_NSS: R12.1, U1.10, U3.5
PROC_SPI1_SCK: U1.7, U3.2
PROC_SYS_JTCK_SWCLK: R9.1, U1.24, U2.4
PROC_SYS_JTDI: R7.1, U1.25, U2.8
PROC_SYS_JTDO_SWO: U1.26, U2.6
PROC_SYS_JTMS_SWDIO: R8.1, U1.23, U2.2
PROC_TIM1_CH2: U1.19, U12.2
PROC_TIM1_CH4: U1.21, U12.3
RST_OUT_U2_JTAG_RST_B: R6.1, U2.10, U10.1
VCC_S1_9V9: C16.1, C17.1, C21.1, C22.1, J1.1, U6.5, U6.8
VCC_TIER1_3V3: C1.1, C2.1, C3.1, C4.1, C5.1, C6.1, C7.1, C10.1, C11.1, C12.1, C15.1, C18.1, C19.1, C20.1, C23.1, C24.1, R1.2, R3.2, R4.2, R6.2, R7.2, R8.2, R12.2, R13.1, R15.2, R16.2, R18.1, U1.1, U1.5, U1.17, U2.1, U3.1, U3.15, U3.16, U5.4, U6.1, U7.6, U10.5, U11.5

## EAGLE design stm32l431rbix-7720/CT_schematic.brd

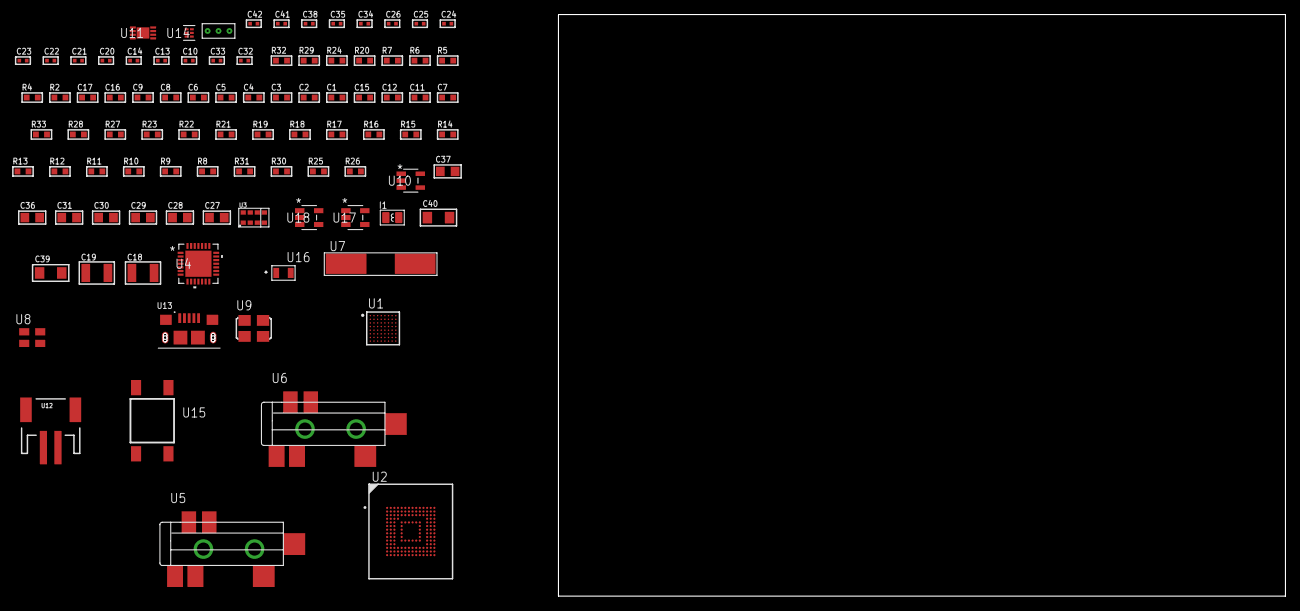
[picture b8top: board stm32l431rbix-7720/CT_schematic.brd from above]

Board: 2 copper layers, 93 parts (0 on the bottom side), 45 nets, no tracks yet.

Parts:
C1, C9, C16, C17: 1e-06; C0603
C2, C3, C4, C5, C6: 1e-07; C0603
C7: 4.7e-06; C0603
C8: 1e-08; C0603
C10, C13, C14, C22, C23, C24, C25, C26, C38: 1e-07; C0402
C11, C12, C15: 2.2e-06; C0603
C18, C19: 2.2e-05; C1210
C20, C21: 1e-09; C0402
C27, C28, C29, C30, C31, C36, C37: 1e-05; C0805
C32, C33: 2.2e-11; C0402
C34, C35, C41, C42: 1e-08; C0402
C39, C40: 1e-05; C1206
I1: 3.3e-06; L0806
R2: 1000.0; R0603
R4, R5: 4700.0; R0603
R6, R7: 2200.0; R0603
R8, R19, R27, R28, R33: 10000.0; R0603
R9, R10, R11, R12, R13, R14, R15, R16, R17, R18: 34000.0; R0603
R20: 22.0; R0603
R21, R22, R23: 47000.0; R0603
R24: 680.0; R0603
R25: 220000.0; R0603
R26: 1000000.0; R0603
R29: 9100.0; R0603
R30: 680000.0; R0603
R31: 120000.0; R0603
R32: 2000.0; R0603
U1: STM32L431RBI6; UFBGA64
U2: mtfc4gmcdm; TFBGA-153
U3: TMD27711; SMD-8
U4: WM8731CLSEFL; QFN-28
U5, U6: SJ-43515TS-SMT-TR
U7: ABLS-12.288MHZ-B4-T
U8: ASEK-32.768KHz-ECST; ASEK
U9: ASFL1-25MHZ-NCS; ASFL1
U10: ltc3406es5; TSOT-23-5
U11: MCP73831T-2ACI/MC; DFN8_2X3MC
U12: S2B-PH-SM4-TB(LF)(SN); JST-2-SMD
U13: 10118193-0001LF; FCI_10118193-0001LF
U14: TPS3895ADRYR; SON-6
U15: 4-1437565-2; SW_4-1437565-2
U16: Q65110A2395; LGM67K-G1J2-24-Z
U17, U18: nc7sz125m5x; NC7SZ125M5X
U19: Dummy; DUMMY_PACKAGE_207

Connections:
CLK_CRYSTAL_U4_1: C32.1, U4.1, U7.1
CLK_CRYSTAL_U4_2: C33.1, U4.2, U7.2
CLK_U1_A1: U1.A1, U8.3
CLK_U1_C1: U1.C1, U9.3
GND: C1.2, C2.2, C3.2, C4.2, C5.2, C6.2, C7.2, C8.2, C9.2, C10.2, C11.2, C12.2, C13.2, C14.2, C15.2, C16.2, C17.2, C21.2, C22.2, C23.2, C24.2, C25.2, C26.2, C27.2, C28.2, C29.2, C30.2, C31.2, C32.2, C33.2, C34.2, C35.2, C36.2, C37.1, C37.2, C38.2, C39.2, C40.2, C41.2, C42.2, R2.2, R8.2, R21.2, R22.2, R23.2, R25.2, R29.2, R31.2, R32.2, U1.C2, U1.D4, U1.D5, U1.D6, U1.F1, U2.C4, U2.E7, U2.G5, U2.H10, U2.K8, U2.N2, U2.N5, U2.P4, U2.P6, U3.3, U4.4, U4.15, U4.19, U4.25, U4.26, U4.29, U5.1, U6.1, U8.2, U9.2, U10.2, U11.6, U11.9, U12.2, U13.5, U13.6, U13.7, U13.8, U13.9, U14.2, U16.C, U17.1, U17.3, U18.1, U18.3, U19.1
INPUT_USBPOWER_5V: C39.1, R33.2, U11.1, U11.2, U13.1
NET_U1_B4: R8.1, U1.B4
NET_U1_C3: R7.1, U1.C3, U3.8
NET_U1_C7: R6.1, U1.C7, U3.2
NET_U1_E1: R5.1, U1.E1, U18.4
NET_U1_H7: U15.3, U15.4
NET_U2_C2: C12.1, C13.1, U2.C2
NET_U2_K5: R4.1, U2.K5, U17.4
NET_U3_4: C17.1, R20.1, U3.4
NET_U3_7: R19.1, U3.7
NET_U4_20: C26.1, C31.1, U4.20
NET_U5_2: C19.1, R22.1, U5.2
NET_U5_5: C18.1, R21.1, U5.5
NET_U6_5: C20.1, C21.1, R23.1, R24.1, U6.5
NET_U10_3: I1.1, U10.3
NET_U10_5: R25.1, R26.1, U10.5
NET_U10_ATNET_3: I1.2, R26.2
NET_U11_5: R33.1, U11.5
NET_U11_8: R32.1, U11.8
NET_U14_1: R28.1, R29.1, U14.1
NET_U14_3: R30.2, R31.1, U14.3
NET_U14_4: R27.1, U14.4, U17.2, U18.2
NET_U15_1: R2.1, U15.1, U15.2
PROC_ADC1_IN1: U1.E3, U19.3
PROC_ADC1_IN2: U1.E2, U19.2
PROC_SAI1_FS_A: U1.H8, U4.9, U4.11
PROC_SAI1_SCK_A: U1.D7, U4.7
PROC_SAI1_SD_A: U1.C6, U4.8
PROC_SDMMC1_CK: R18.1, U1.C5, U2.M6
PROC_SDMMC1_CMD: R17.1, U1.B5, U2.M5
PROC_SDMMC1_D0: R9.1, U1.E8, U2.A3
PROC_SDMMC1_D1: R10.1, U1.D8, U2.A4
PROC_SDMMC1_D2: R11.1, U1.B7, U2.A5
PROC_SDMMC1_D3: R12.1, U1.B6, U2.B2
PROC_SDMMC1_D4: R13.1, U1.B3, U2.B3
PROC_SDMMC1_D5: R14.1, U1.A3, U2.B4
PROC_SDMMC1_D6: R15.1, U1.F6, U2.B5
PROC_SDMMC1_D7: R16.1, U1.E7, U2.B6
VCC_S1_3V7: C36.1, C40.1, U10.4, U11.3, U11.4, U12.1
VCC_TIER1_3V3: C1.1, C2.1, C3.1, C4.1, C5.1, C6.1, C7.1, C8.1, C9.1, C10.1, C11.1, C14.1, C15.1, C16.1, C22.1, C23.1, C24.1, C25.1, C27.1, C28.1, C29.1, C30.1, C34.1, C35.1, C37.2, C38.1, C41.1, C42.1, I1.2, R4.2, R5.2, R6.2, R7.2, R9.2, R10.2, R11.2, R12.2, R13.2, R14.2, R15.2, R16.2, R17.2, R18.2, R19.2, R20.2, R26.2, R27.2, R28.2, R30.1, U1.B2, U1.D2, U1.E4, U1.E5, U1.E6, U1.H1, U2.C6, U2.E6, U2.F5, U2.J10, U2.K9, U2.M4, U2.N4, U2.P3, U2.P5, U3.1, U4.3, U4.5, U4.12, U4.18, U8.4, U9.4, U14.6, U17.5, U18.5
